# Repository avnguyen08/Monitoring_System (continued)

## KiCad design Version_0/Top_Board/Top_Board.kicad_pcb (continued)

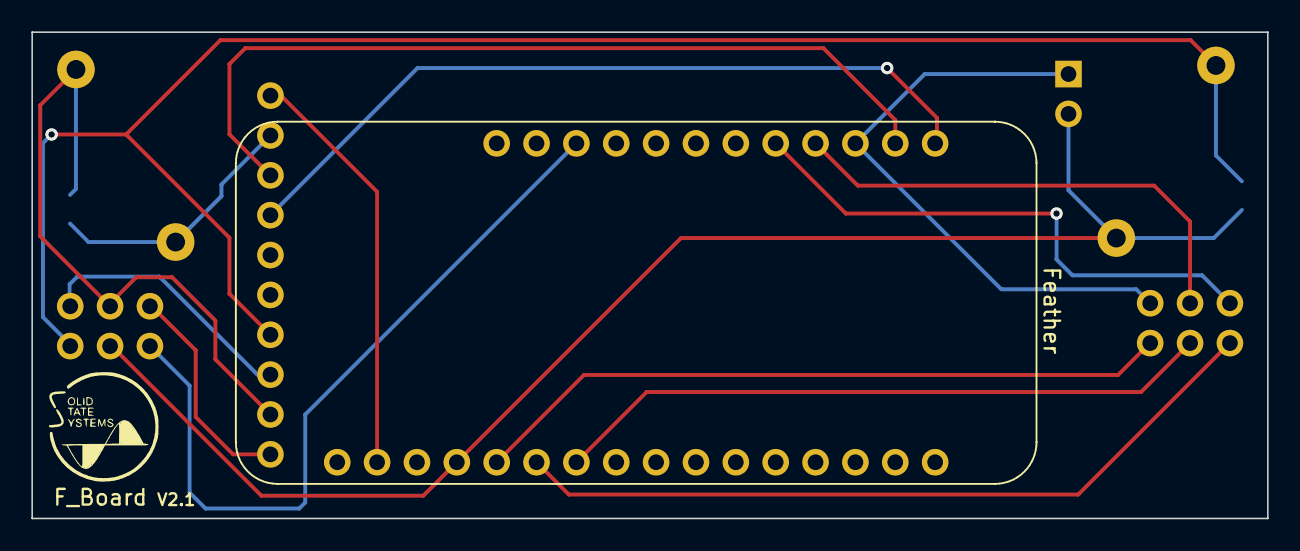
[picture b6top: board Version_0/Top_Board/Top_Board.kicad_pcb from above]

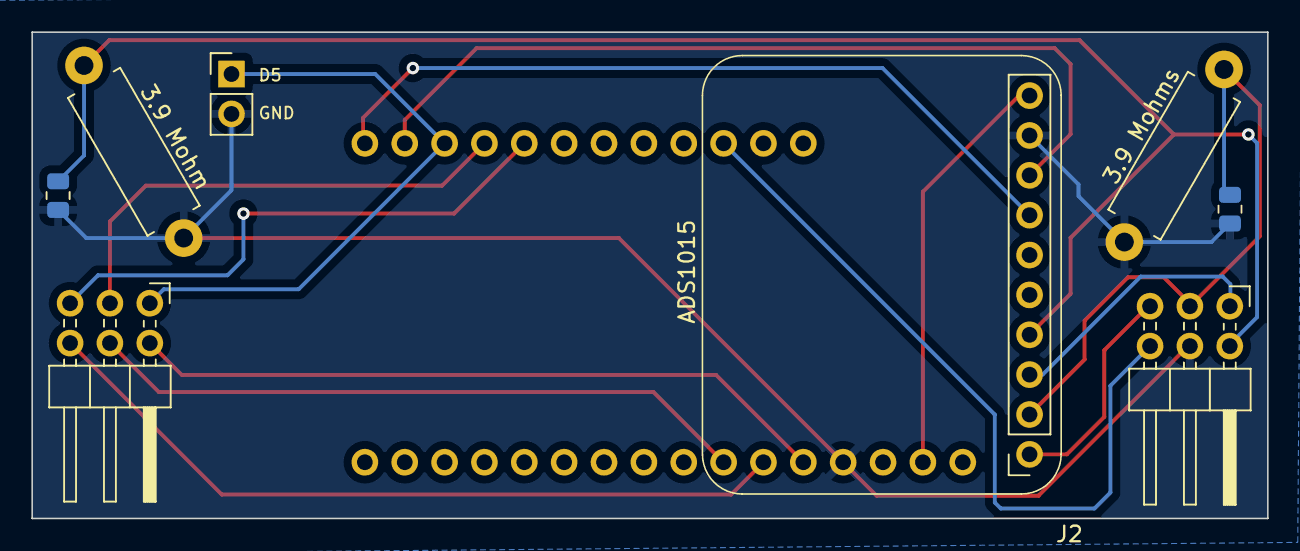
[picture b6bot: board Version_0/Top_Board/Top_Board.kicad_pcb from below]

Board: 2 copper layers, 78.7 x 31.0 mm, 9 parts (8 on the bottom side), 15 nets.

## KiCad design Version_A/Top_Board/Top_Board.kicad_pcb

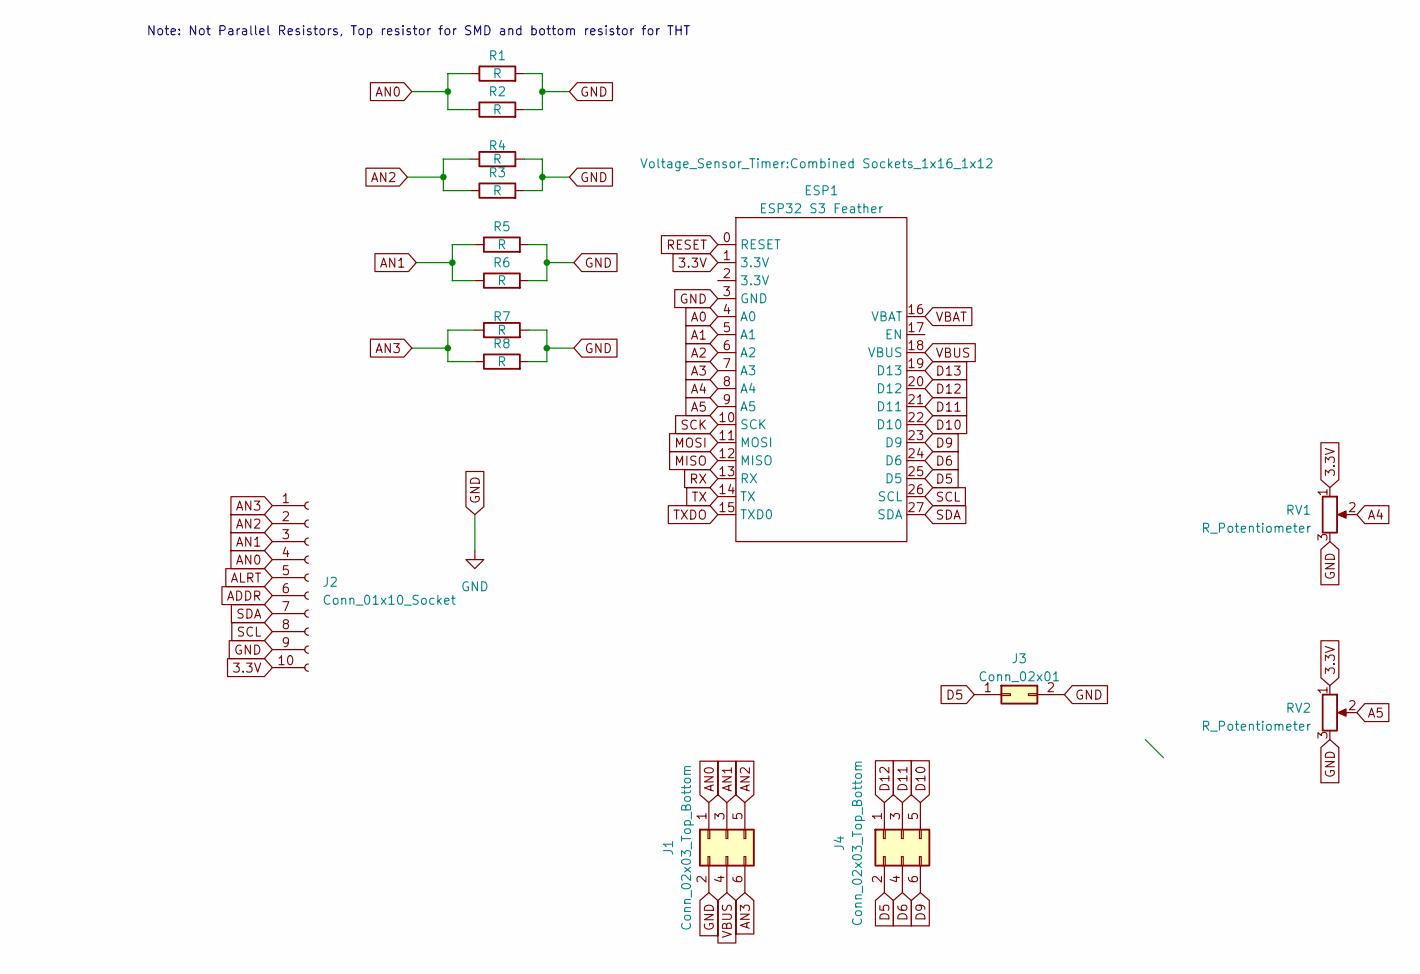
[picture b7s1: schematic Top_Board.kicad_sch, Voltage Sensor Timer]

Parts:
ESP1: ESP32 S3 Feather; Combined Sockets_1x16_1x12
J1, J4: Conn_02x03_Top_Bottom; PinHeader_2x03_P2.54mm_Horizontal
J2: Conn_01x10_Socket; PinSocket_1x10_P2.54mm_Vertical_1
J3: Conn_02x01; PinHeader_1x02_P2.54mm_Vertical
R1, R4, R5, R7: R; R_0805_2012Metric
R2, R3, R6, R8: R; R_Axial_DIN0411_L9.9mm_D3.6mm_P12.70mm_Horizontal
RV1, RV2: R_Potentiometer; SSS_Potentiometer

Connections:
3.3V: ESP1.1 (3.3V), J2.10, RV1.1, RV2.1
A0: ESP1.4 (A0)
A1: ESP1.5 (A1)
A2: ESP1.6 (A2)
A3: ESP1.7 (A3)
A4: ESP1.8 (A4), RV1.2
A5: ESP1.9 (A5), RV2.2
ADDR: J2.6
ALRT: J2.5
AN0: J1.1, J2.4, R1.1, R2.1
AN1: J1.3, J2.3, R5.1, R6.1
AN2: J1.5, J2.2, R3.1, R4.1
AN3: J1.6, J2.1, R7.1, R8.1
D5: ESP1.25 (D5), J3.1, J4.2
D6: ESP1.24 (D6), J4.4
D9: ESP1.23 (D9), J4.6
D10: ESP1.22 (D10), J4.5
D11: ESP1.21 (D11), J4.3
D12: ESP1.20 (D12), J4.1
D13: ESP1.19 (D13)
GND: ESP1.3 (GND), J1.2, J2.9, J3.2, R1.2, R2.2, R3.2, R4.2, R5.2, R6.2, R7.2, R8.2, RV1.3, RV2.3
MISO: ESP1.12 (MISO)
MOSI: ESP1.11 (MOSI)
RESET: ESP1.0 (RESET)
RX: ESP1.13 (RX)
SCK: ESP1.10 (SCK)
SCL: ESP1.26 (SCL), J2.8
SDA: ESP1.27 (SDA), J2.7
TX: ESP1.14 (TX)
TXDO: ESP1.15 (TXD0)
VBAT: ESP1.16 (VBAT)
VBUS: ESP1.18 (VBUS), J1.4

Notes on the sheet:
Note: Not Parallel Resistors, Top resistor for SMD and bottom resistor for THT

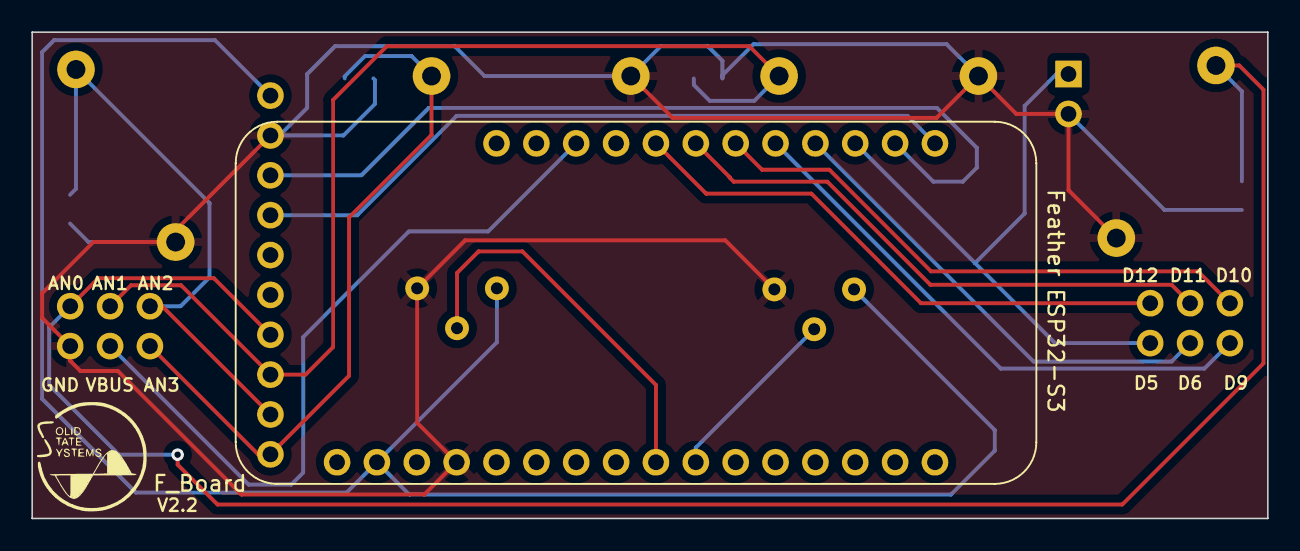
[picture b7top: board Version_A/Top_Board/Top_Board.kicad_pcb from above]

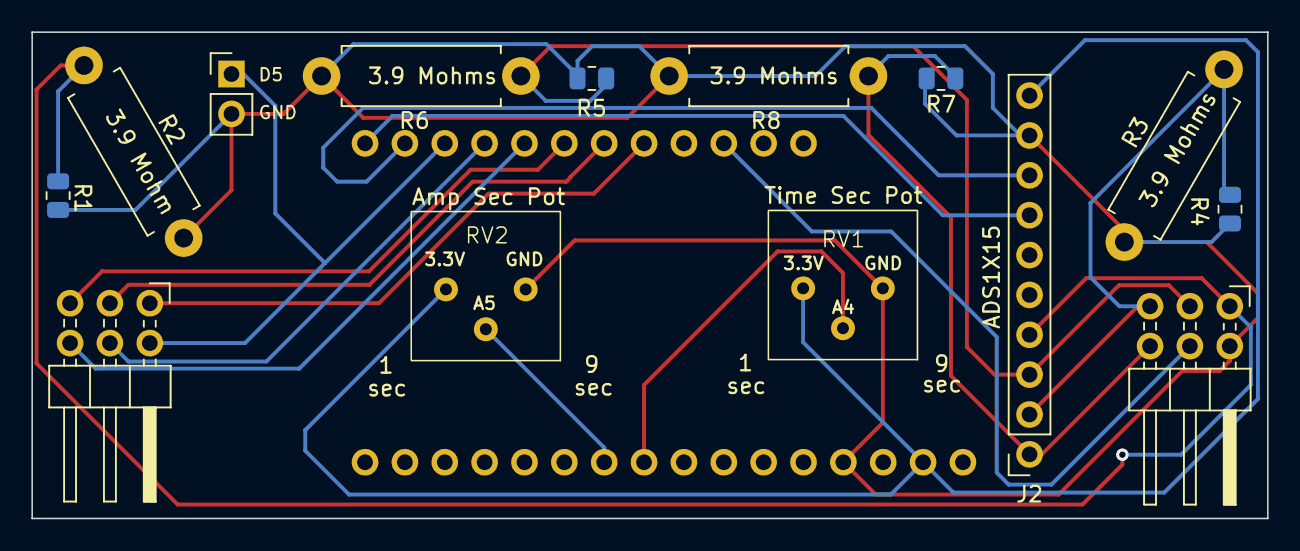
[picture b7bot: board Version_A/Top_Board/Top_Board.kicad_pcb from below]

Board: 2 copper layers, 78.7 x 31.0 mm, 15 parts (14 on the bottom side), 17 nets.

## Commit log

2023-09-01 work comp sample
2023-11-09 comment and aesthetic changes
2023-12-18 Legacy Repository
2023-12-18 rework of project directory
2023-12-18 organization updates
2023-12-19 updated board b
2023-12-19 added hardware filter simulation
2023-12-20 adjusted hardware values
2023-12-20 freeRTOS rework with Waveform class function and reorganization of folder
2023-12-22 reorganized class and functions
2023-12-22 updated comments
2023-12-24 updated simulation circuit and finalized hardware design?
2024-01-05 connected e60 ground and an1
2024-01-06 testing double buffer
2024-01-06 percentage based truncations
2024-01-14 dummy proofing and code rearranging
2024-01-15 added config switch for hardware filter on and off
2024-01-17 fixed timing issue and made averaging for HW Filter
2024-01-19 triangle wave simulation
2024-01-22 added WDT
2024-02-19 1st test for better accuracy
2024-02-19 alternate tests diff board
2024-02-20 working software filter
2024-02-20 changed 5 pin to 4 pin term block
2024-02-20 soft pcb changes: 90 degree term block, din connector scooted in, connected grounds
2024-02-24 ads1015 on bottom board and aesthetic changes
2024-02-24 90 degree terminal block added
2024-02-25 small changes
2024-02-25 autosaves and csv
2024-02-26 kicad 8.0 file
2024-03-03 csv file change and code update
2024-03-04 readjusted graphics and dip switches, increased serial rate, opened d17,d18 tx rx
2024-03-06 added flash folder and adjusted GUI
2024-03-06 readme updated with picture
2024-03-06 aesthetic readme
2024-03-07 updated instructions
2024-03-15 minor fixe
2024-03-15 gui update
2024-03-19 updated jlpcb format
2024-03-20 Simulation comments
2024-03-20 gui update/ads1115
2024-03-24 aesthetic changes
2024-03-29 testing multiplier readings
2024-04-03 1.07 fixes
2024-04-05 test
2024-04-05 black boards flash
2024-04-10 1.09 version
2025-07-18 switched B and C directories
2025-07-18 merged ads1115 into main branch
2025-07-18 fixed directory overwrite
